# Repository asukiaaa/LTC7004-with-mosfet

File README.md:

# LTC7004-with-MOSFET

## Components

- [LTC7004](https://www.digikey.jp/product-detail/ja/analog-devices-inc/LTC7004EMSE-TRPBF/LTC7004EMSE-TRPBFCT-ND/9385382)
- [Terminal block 9.53mm](https://www.digikey.jp/product-detail/ja/phoenix-contact/1714971/277-1271-ND/260639)
- [MOSFET 80V 28A 2.1mΩ](https://www.digikey.jp/product-detail/ja/on-semiconductor/NVMFS6H800NWFT1G/NVMFS6H800NWFT1G-ND/8636599) or [MOSFET 80V 28A 2.1mΩ](https://www.digikey.jp/product-detail/ja/on-semiconductor/NVMFS6H800NT1G/NVMFS6H800NT1GOSCT-ND/9169185)
- [Grove connector](https://www.seeedstudio.com/Grove-Universal-4-pin-connector.html) or PH2.0 4P connector
- [Varistor 82V 1206inch 3216mm](https://www.digikey.jp/product-detail/ja/bourns-inc/ZV50K1206121NIR1HT/118-ZV50K1206121NIR1HTCT-ND/11585444)

Other MOSFETS that I considered.
- [MOSFET 80V 240A 1.9mΩ](https://www.digikey.jp/product-detail/ja/infineon-technologies/IAUT240N08S5N019ATMA1/IAUT240N08S5N019ATMA1CT-ND/8818762) * 2
- [MOSFET 80V 23A 2.8mΩ](https://www.digikey.jp/product-detail/ja/on-semiconductor/NTMFS6H801NT1G/NTMFS6H801NT1GOSCT-ND/8024461) * 3
- [MOSFET 60V 43A 1.1mΩ](https://www.digikey.jp/product-detail/ja/on-semiconductor/FDMT80060DC/FDMT80060DCCT-ND/5414002)
- [MOSFET 60V 80A 900uΩ](https://www.digikey.jp/product-detail/ja/on-semiconductor/NVBLS001N06C/488-NVBLS001N06CCT-ND/11593187)
- [MOSFET 60V 54A 750uΩ](https://www.digikey.jp/product-detail/ja/on-semiconductor/NVBLS0D7N06C/488-NVBLS0D7N06CCT-ND/11593286)

## License

MIT

## References

- [Eval bode DC2750A schematic](https://www.analog.com/media/en/technical-documentation/eval-board-schematic/DC2750A-1-SCH.PDF)

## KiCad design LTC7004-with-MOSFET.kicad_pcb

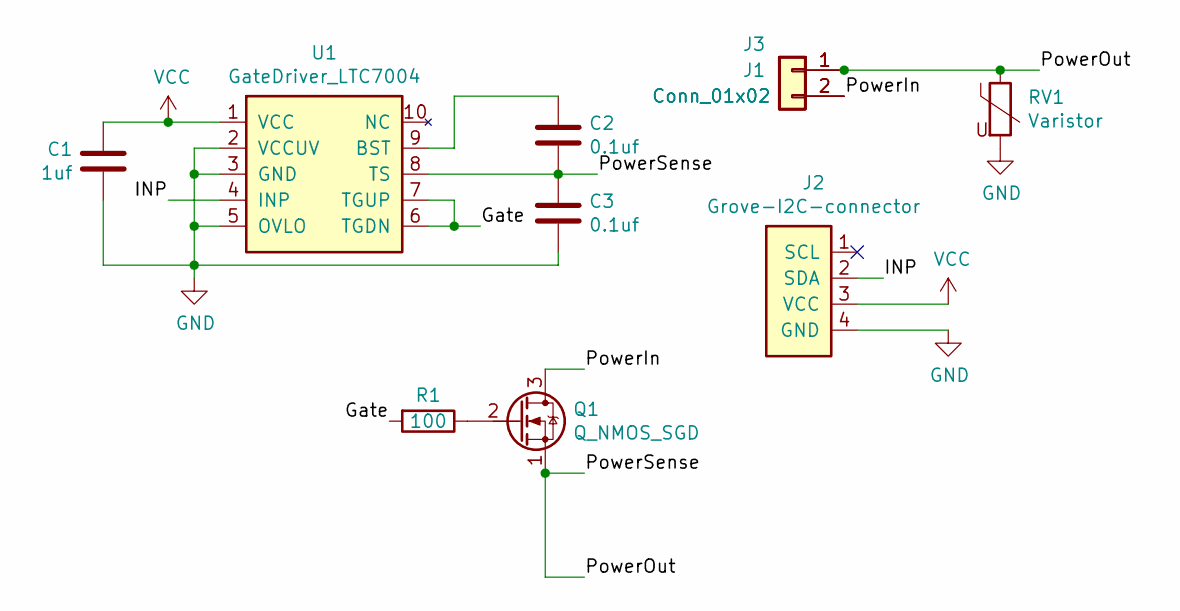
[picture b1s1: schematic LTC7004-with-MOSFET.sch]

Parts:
C1: 1uf; C_0603_1608Metric
C2, C3: 0.1uf; C_0603_1608Metric
J1: Conn_01x02; Terminal_9.52mm_1x02_1714971
J2: Grove-I2C-connector; NS-Tech_Grove_1x04_P2mm_Vertical
J3: Conn_01x02; TerminalBlock_Phoenix_MKDS-1,5-2-5.08_1x02_P5.08mm_Horizont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
Q1: Q_NMOS_SGD; DFN5
R1: 100; R_0603_1608Metric
RV1: Varistor; R_1206_3216Metric
U1: GateDriver_LTC7004

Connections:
/Gate: R1.2, U1.6 (TGDN), U1.7 (TGUP)
/INP: J2.2 (SDA), U1.4 (INP)
/PowerIn: J1.2, J3.2, Q1.3 (D)
/PowerOut: C2.2, C3.1, J1.1, J3.1, Q1.1 (S), RV1.1, U1.8 (TS)
GND: C1.1, C3.2, J2.4 (GND), RV1.2, U1.2 (VCCUV), U1.3 (GND), U1.5 (OVLO), U1.11 (GND)
unnamed: C2.1, U1.9 (BST)
unnamed: Q1.2 (G), R1.1
VCC: C1.2, J2.3 (VCC), U1.1 (VCC)

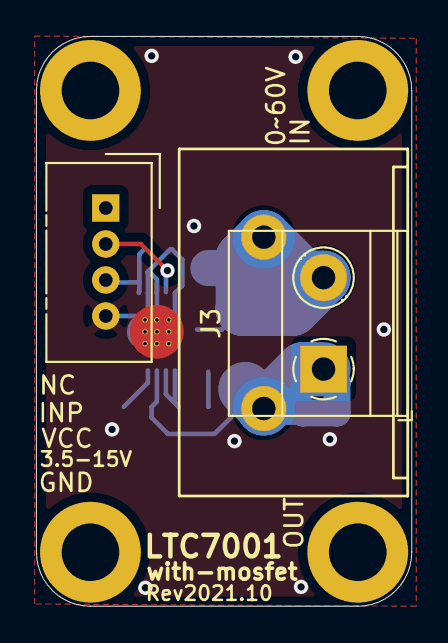
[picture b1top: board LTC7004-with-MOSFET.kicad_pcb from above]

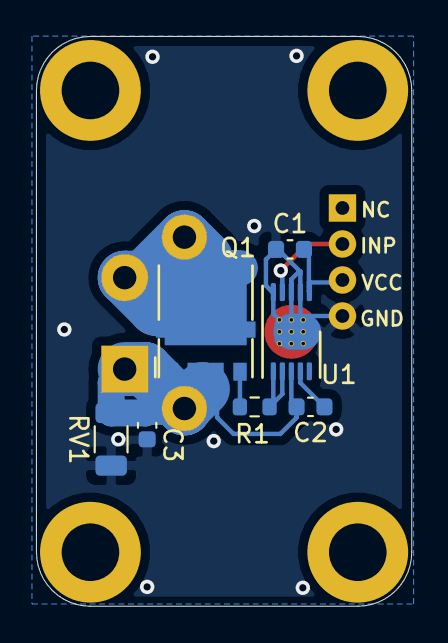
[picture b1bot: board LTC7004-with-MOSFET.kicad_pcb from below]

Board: 2 copper layers, 20.8 x 31.7 mm, 10 parts (7 on the bottom side), 8 nets.

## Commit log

2021-07-22 Add explanation about considered before mosfets
2021-07-22 Add link of grove connector
2021-09-06 Add second mosfet
2021-10-22 Add condensor, resistor and varistor
